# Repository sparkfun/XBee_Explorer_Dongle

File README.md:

SparkFun XBee Explorer Dongle
========================================

[*SparkFun XBee Explorer Dongle (WRL-11697)*](https://www.sparkfun.com/products/11697)

With the XBee Explorer Dongle you can plug the unit directly into your USB port 
and have it act as a gateway between your computer and the XBee. It has the FT231X USB-to-serial converter IC on board. 

Repository Contents
-------------------
* **/Hardware** - All Eagle design files (.brd, .sch, .STL)
* **/Production** - Test bed files and production panel files

Documentation
--------------
* **[Hookup Guide](https://learn.sparkfun.com/tutorials/exploring-xbees-and-xctu)** - Basic hookup guide for the XBee Explorer.
* **[SparkFun Fritzing repo](https://github.com/sparkfun/Fritzing_Parts)** - Fritzing diagrams for SparkFun products.
* **[SparkFun 3D Model repo](https://github.com/sparkfun/3D_Models)** - 3D models of SparkFun products. 

Product Versions
----------------
* [WRL-11697](https://www.sparkfun.com/products/11697)- XBee Dongle with the FT232 USB to serial converter, v23. Current.
* [WRL-09819](https://www.sparkfun.com/products/retired/9819)- XBee Dongle with the FT232 USB to serial converter, v12. Retired.

Version History
---------------
* [V_2.3](https://github.com/sparkfun/XBee_Explorer_Dongle/tree/V_2.3) - GitHub files, version 2.3. Current
* [V_2.2](https://github.com/sparkfun/XBee_Explorer_Dongle/tree/V_2.2) - GitHub files, version 2.2
* [V_1.2](https://github.com/sparkfun/XBee_Explorer_Dongle/tree/V_1.2) -GitHub files, version 1.2. 

License Information
-------------------

This product is _**open source**_! 

Please review the LICENSE.md file for license information. 

If you have any questions or concerns on licensing, please contact techsupport@sparkfun.com.

Distributed as-is; no warranty is given.

- Your friends at SparkFun.

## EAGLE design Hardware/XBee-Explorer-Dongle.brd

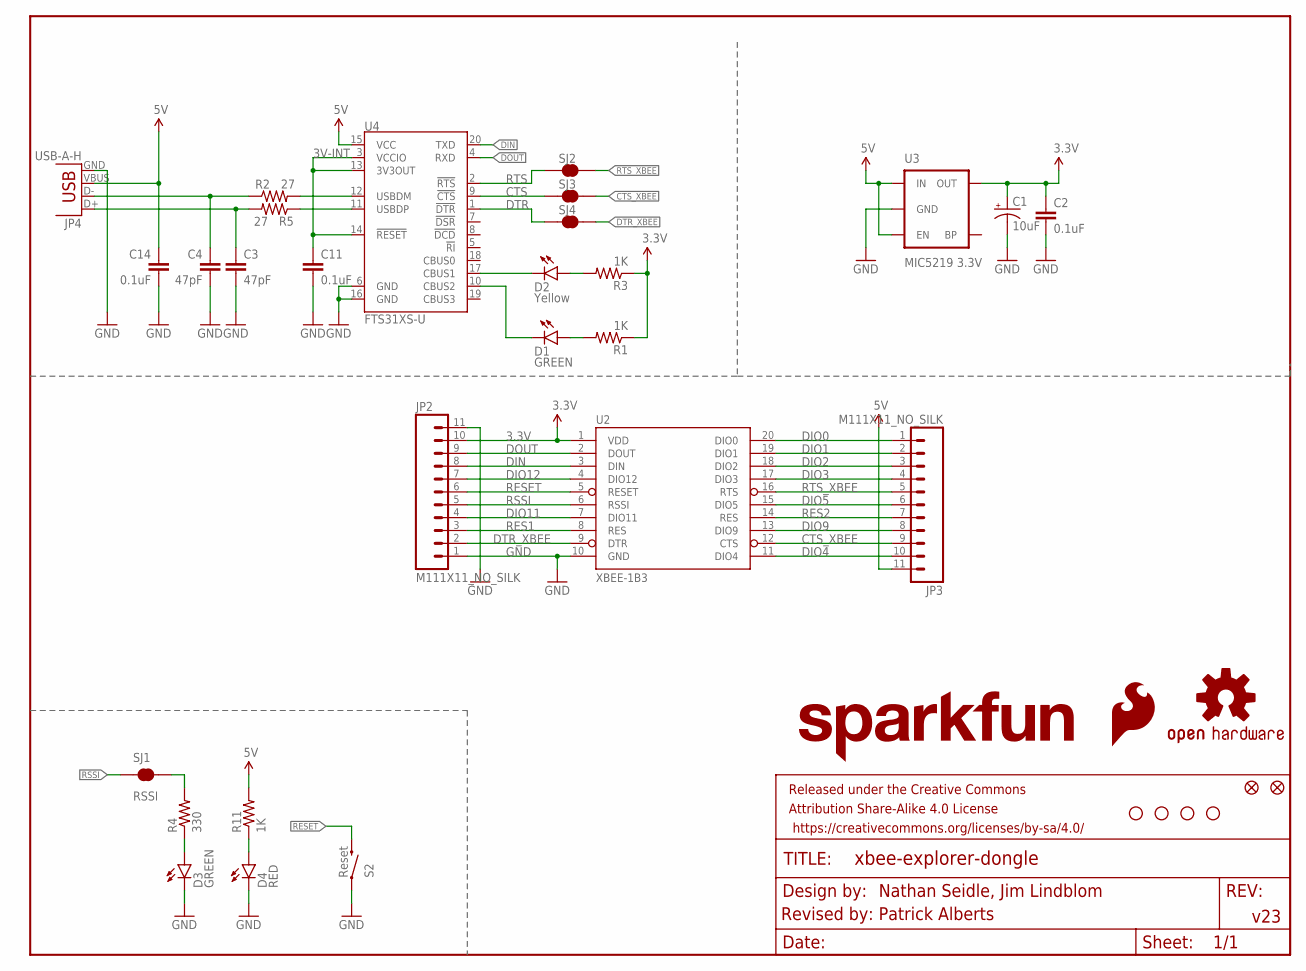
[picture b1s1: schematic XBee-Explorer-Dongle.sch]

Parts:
C1: 10uF; EIA3216
C2, C11, C14: 0.1uF; 0603-CAP
C3, C4: 47pF; 0603-CAP
D1, D3: GREEN; LED-0603
D2: Yellow; LED-0603
D4: RED; LED-0603
FID1, FID2: FIDUCIAL1X2; FIDUCIAL-1X2
FRAME1: FRAME-LETTER; CREATIVE_COMMONS
JP2, JP3: M111X11_NO_SILK; 1X11_NO_SILK
JP4: USB-A-H
LOGO1: SFE_LOGO_FLAME.1_INCH; SFE_LOGO_FLAME_.1
LOGO2: SFE_LOGO_NAME.2_INCH; SFE_LOGO_NAME_.2
R1, R3, R11: 1K; 0603-RES
R2, R5: 27; 0603-RES
R4: 330; 0603-RES
S2: Reset; TACTILE_SWITCH_SMD
SJ1, SJ2, SJ3, SJ4: RSSI; SJ_2S-TRACE
U2: XBEE-1B3; XBEE-SMD
U3: MIC5219 3.3V; SOT23-5
U4: FTS31XS-U; SSOP20_L
U$5, U$9, U$10, U$11: STAND-OFF
U$7: OSHW-LOGOS; OSHW-LOGO-S

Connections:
3.3V: C1.A (+), C2.1, JP2.10, R1.1, R3.1, U2.1 (VDD), U3.5 (OUT)
3V-INT: C11.1, U4.3 (VCCIO), U4.13 (3V3OUT), U4.14 (!RESET)
5V: C14.1, JP3.11, JP4.VBUS, R11.2, U3.1 (IN), U3.3 (EN), U4.15 (VCC)
CTS: SJ3.1, U4.9 (!CTS)
CTS_XBEE: JP3.9, SJ3.2, U2.12 (CTS)
DIN: JP2.8, U2.3 (DIN), U4.20 (TXD)
DIO0: JP3.1, U2.20 (DIO0)
DIO1: JP3.2, U2.19 (DIO1)
DIO2: JP3.3, U2.18 (DIO2)
DIO3: JP3.4, U2.17 (DIO3)
DIO4: JP3.10, U2.11 (DIO4)
DIO5: JP3.6, U2.15 (DIO5)
DIO9: JP3.8, U2.13 (DIO9)
DIO11: JP2.4, U2.7 (DIO11)
DIO12: JP2.7, U2.4 (DIO12)
DOUT: JP2.9, U2.2 (DOUT), U4.4 (RXD)
DTR: SJ4.1, U4.1 (!DTR)
DTR_XBEE: JP2.2, SJ4.2, U2.9 (DTR)
GND: C1.C (-), C2.2, C3.2, C4.2, C11.2, C14.2, D3.C, D4.C, JP2.1, JP2.11, JP4.GND, S2.1, U2.10 (GND), U3.2 (GND), U4.6 (GND), U4.16 (GND)
unnamed: D1.A, R1.2
unnamed: D3.A, R4.1
unnamed: C4.1, JP4.D-, R2.1
unnamed: D2.A, R3.2
unnamed: R2.2, U4.12 (USBDM)
unnamed: C3.1, JP4.D+, R5.2
unnamed: R5.1, U4.11 (USBDP)
unnamed: R4.2, SJ1.2
unnamed: D4.A, R11.1
RES1: JP2.3, U2.8 (RES)
RES2: JP3.7, U2.14 (RES)
RESET: JP2.6, S2.3 (2), U2.5 (RESET)
RSSI: JP2.5, SJ1.1, U2.6 (RSSI)
RTS: SJ2.1, U4.2 (!RTS)
RTS_XBEE: JP3.5, SJ2.2, U2.16 (RTS)
RXLED: D2.C, U4.17 (CBUS1)
TXLED: D1.C, U4.10 (CBUS2)

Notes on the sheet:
Nathan Seidle, Jim Lindblom
v23
Revised by: Patrick Alberts

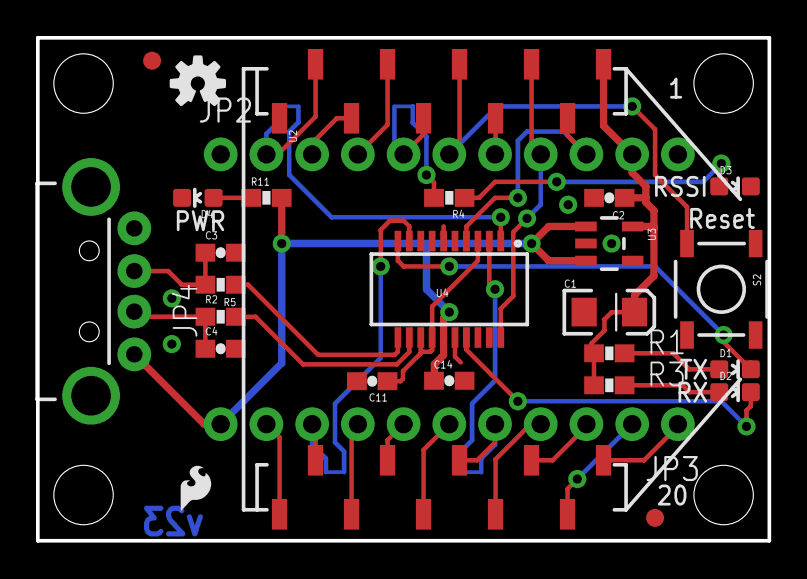
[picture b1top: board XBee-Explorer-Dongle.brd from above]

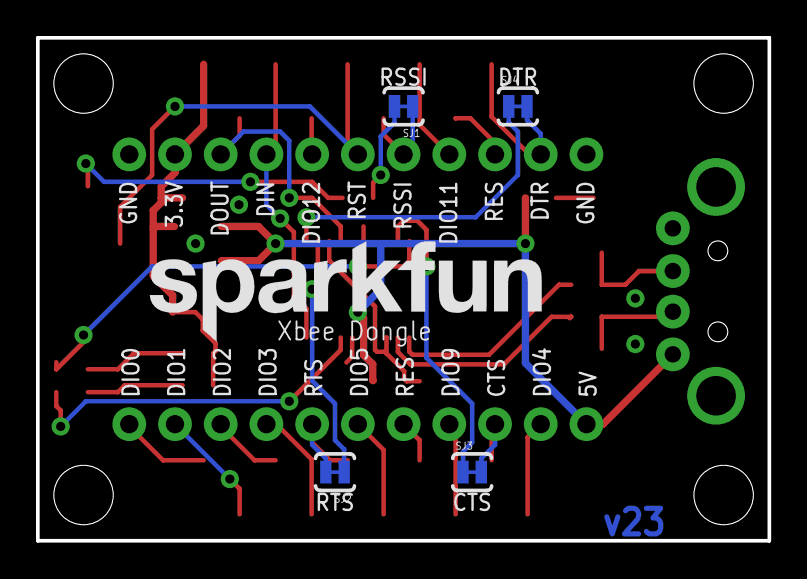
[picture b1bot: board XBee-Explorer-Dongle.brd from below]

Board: 2 copper layers, 40.6 x 27.9 mm, 37 parts (5 on the bottom side), 36 nets.

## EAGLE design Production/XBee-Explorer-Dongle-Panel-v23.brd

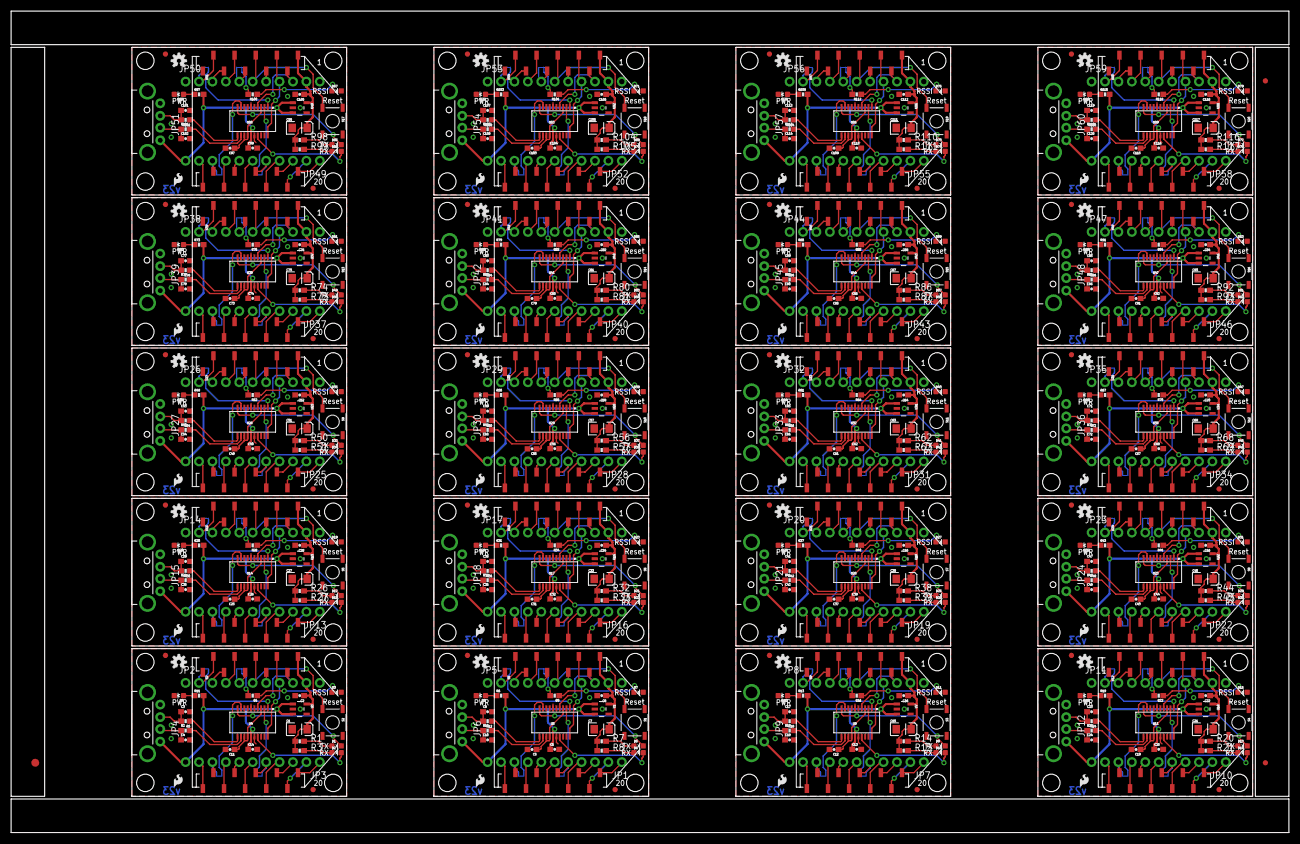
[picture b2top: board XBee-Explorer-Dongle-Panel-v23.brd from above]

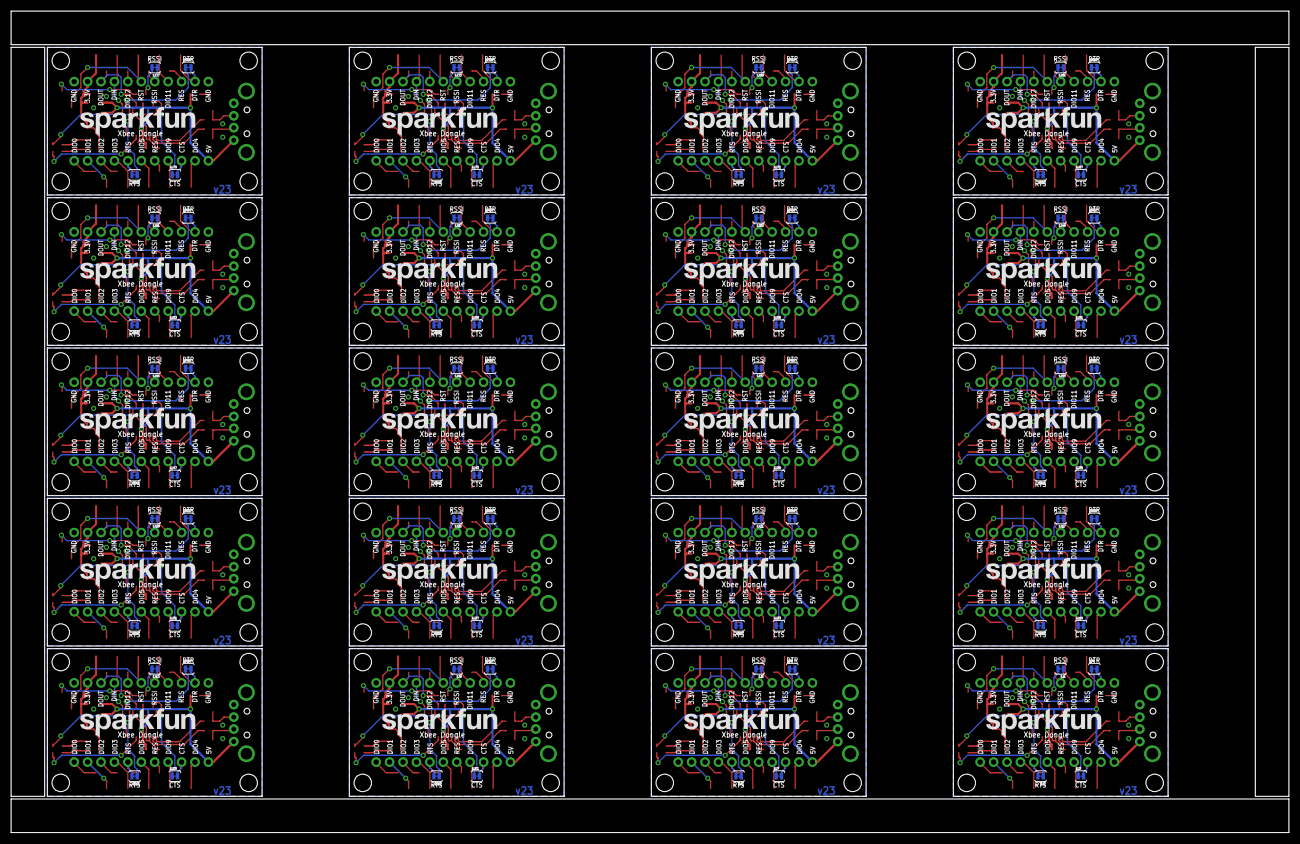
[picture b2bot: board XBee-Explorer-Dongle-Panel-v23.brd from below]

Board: 2 copper layers, 241.8 x 155.4 mm, 723 parts (100 on the bottom side), 720 nets.

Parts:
C1, C7, C15, C21, C27, C33, C39, C45, C51, C57, C63, C69, C75, C81, C87, C93, C99, C105, C111, C117: 10uF; EIA3216
C2, C5, C6, C8, C11, C12, C13, C14, C16, C19, C20, C22, C25, C26, C28, C31, C32, C34, C37, C38, C40, C43, C44, C46, C49, C50, C52, C55, C56, C58, C61, C62, C64, C67, C68, C70, C73, C74, C76, C79, C80, C82, C85, C86, C88, C91, C92, C94, C97, C98, C100, C103, C104, C106, C109, C110, C112, C115, C116, C118: 0.1uF; 0603-CAP
C3, C4, C9, C10, C17, C18, C23, C24, C29, C30, C35, C36, C41, C42, C47, C48, C53, C54, C59, C60, C65, C66, C71, C72, C77, C78, C83, C84, C89, C90, C95, C96, C101, C102, C107, C108, C113, C114, C119, C120: 47pF; 0603-CAP
D1, D3, D5, D7, D9, D11, D13, D15, D17, D19, D21, D23, D25, D27, D29, D31, D33, D35, D37, D39, D41, D43, D45, D47, D49, D51, D53, D55, D57, D59, D61, D63, D65, D67, D69, D71, D73, D75, D77, D79: GREEN; LED-0603
D2, D6, D10, D14, D18, D22, D26, D30, D34, D38, D42, D46, D50, D54, D58, D62, D66, D70, D74, D78: Yellow; LED-0603
D4, D8, D12, D16, D20, D24, D28, D32, D36, D40, D44, D48, D52, D56, D60, D64, D68, D72, D76, D80: RED; LED-0603
E$1: FIDUCIAL-1.5X3
E$5, E$6: FIDUCIAL-1X2
FID1, FID2, FID3, FID4, FID5, FID6, FID7, FID8, FID9, FID10, FID11, FID12, FID13, FID14, FID15, FID16, FID17, FID18, FID19, FID20, FID21, FID22, FID23, FID24, FID25, FID26, FID27, FID28, FID29, FID30, FID31, FID32, FID33, FID34, FID35, FID36, FID37, FID38, FID39, FID40: FIDUCIAL1X2; FIDUCIAL-1X2
JP1, JP2, JP3, JP5, JP7, JP8, JP10, JP11, JP13, JP14, JP16, JP17, JP19, JP20, JP22, JP23, JP25, JP26, JP28, JP29, JP31, JP32, JP34, JP35, JP37, JP38, JP40, JP41, JP43, JP44, JP46, JP47, JP49, JP50, JP52, JP53, JP55, JP56, JP58, JP59: M111X11_NO_SILK; 1X11_NO_SILK
JP4, JP6, JP9, JP12, JP15, JP18, JP21, JP24, JP27, JP30, JP33, JP36, JP39, JP42, JP45, JP48, JP51, JP54, JP57, JP60: USB-A-H
LOGO1, LOGO3, LOGO5, LOGO7, LOGO9, LOGO11, LOGO13, LOGO15, LOGO17, LOGO19, LOGO21, LOGO23, LOGO25, LOGO27, LOGO29, LOGO31, LOGO33, LOGO35, LOGO37, LOGO39: SFE_LOGO_FLAME.1_INCH; SFE_LOGO_FLAME_.1
LOGO2, LOGO4, LOGO6, LOGO8, LOGO10, LOGO12, LOGO14, LOGO16, LOGO18, LOGO20, LOGO22, LOGO24, LOGO26, LOGO28, LOGO30, LOGO32, LOGO34, LOGO36, LOGO38, LOGO40: SFE_LOGO_NAME.2_INCH; SFE_LOGO_NAME_.2
R1, R3, R6, R7, R8, R11, R13, R14, R15, R19, R20, R21, R25, R26, R27, R31, R32, R33, R37, R38, R39, R43, R44, R45, R49, R50, R51, R55, R56, R57, R61, R62, R63, R67, R68, R69, R73, R74, R75, R79, R80, R81, R85, R86, R87, R91, R92, R93, R97, R98, R99, R103, R104, R105, R109, R110, R111, R115, R116, R117: 1K; 0603-RES
R2, R5, R10, R12, R17, R18, R23, R24, R29, R30, R35, R36, R41, R42, R47, R48, R53, R54, R59, R60, R65, R66, R71, R72, R77, R78, R83, R84, R89, R90, R95, R96, R101, R102, R107, R108, R113, R114, R119, R120: 27; 0603-RES
R4, R9, R16, R22, R28, R34, R40, R46, R52, R58, R64, R70, R76, R82, R88, R94, R100, R106, R112, R118: 330; 0603-RES
S1, S2, S3, S4, S5, S6, S7, S8, S9, S10, S11, S12, S13, S14, S15, S16, S17, S18, S19, S20: Reset; TACTILE_SWITCH_SMD
SJ1, SJ2, SJ3, SJ4, SJ5, SJ6, SJ7, SJ8, SJ9, SJ10, SJ11, SJ12, SJ13, SJ14, SJ15, SJ16, SJ17, SJ18, SJ19, SJ20, SJ21, SJ22, SJ23, SJ24, SJ25, SJ26, SJ27, SJ28, SJ29, SJ30, SJ31, SJ32, SJ33, SJ34, SJ35, SJ36, SJ37, SJ38, SJ39, SJ40, SJ41, SJ42, SJ43, SJ44, SJ45, SJ46, SJ47, SJ48, SJ49, SJ50, SJ51, SJ52, SJ53, SJ54, SJ55, SJ56, SJ57, SJ58, SJ59, SJ60, SJ61, SJ62, SJ63, SJ64, SJ65, SJ66, SJ67, SJ68, SJ69, SJ70, SJ71, SJ72, SJ73, SJ74, SJ75, SJ76, SJ77, SJ78, SJ79, SJ80: RSSI; SJ_2S-TRACE
U1, U3, U7, U10, U13, U16, U19, U22, U25, U28, U31, U34, U37, U40, U43, U46, U49, U52, U55, U58: MIC5219 3.3V; SOT23-5
U2, U6, U9, U12, U15, U18, U21, U24, U27, U30, U33, U36, U39, U42, U45, U48, U51, U54, U57, U60: XBEE-1B3; XBEE-SMD
U4, U5, U8, U11, U14, U17, U20, U23, U26, U29, U32, U35, U38, U41, U44, U47, U50, U53, U56, U59: FTS31XS-U; SSOP20_L
U$1, U$2, U$3, U$4, U$5, U$8, U$9, U$10, U$11, U$12, U$13, U$14, U$16, U$17, U$18, U$19, U$21, U$22, U$23, U$24, U$26, U$27, U$28, U$29, U$31, U$32, U$33, U$34, U$36, U$37, U$38, U$39, U$41, U$42, U$43, U$44, U$46, U$47, U$48, U$49, U$51, U$52, U$53, U$54, U$56, U$57, U$58, U$59, U$61, U$62, U$63, U$64, U$66, U$67, U$68, U$69, U$71, U$72, U$73, U$74, U$76, U$77, U$78, U$79, U$81, U$82, U$83, U$84, U$86, U$87, U$88, U$89, U$91, U$92, U$93, U$94, U$96, U$97, U$98, U$99: STAND-OFF
U$6, U$7, U$15, U$20, U$25, U$30, U$35, U$40, U$45, U$50, U$55, U$60, U$65, U$70, U$75, U$80, U$85, U$90, U$95, U$100: OSHW-LOGOS; OSHW-LOGO-S

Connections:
3.3V: C1.A, C2.1, JP2.10, R1.1, R3.1, U2.1, U3.5
3.3V1: C7.A, C8.1, JP5.10, R7.1, R8.1, U1.5, U6.1
3.3V2: C15.A, C16.1, JP8.10, R14.1, R15.1, U7.5, U9.1
3.3V3: C21.A, C22.1, JP11.10, R20.1, R21.1, U10.5, U12.1
3.3V4: C27.A, C28.1, JP14.10, R26.1, R27.1, U13.5, U15.1
3.3V5: C33.A, C34.1, JP17.10, R32.1, R33.1, U16.5, U18.1
3.3V6: C39.A, C40.1, JP20.10, R38.1, R39.1, U19.5, U21.1
3.3V7: C45.A, C46.1, JP23.10, R44.1, R45.1, U22.5, U24.1
3.3V8: C51.A, C52.1, JP26.10, R50.1, R51.1, U25.5, U27.1
3.3V9: C57.A, C58.1, JP29.10, R56.1, R57.1, U28.5, U30.1
3.3V10: C63.A, C64.1, JP32.10, R62.1, R63.1, U31.5, U33.1
3.3V11: C69.A, C70.1, JP35.10, R68.1, R69.1, U34.5, U36.1
3.3V12: C75.A, C76.1, JP38.10, R74.1, R75.1, U37.5, U39.1
3.3V13: C81.A, C82.1, JP41.10, R80.1, R81.1, U40.5, U42.1
3.3V14: C87.A, C88.1, JP44.10, R86.1, R87.1, U43.5, U45.1
3.3V15: C93.A, C94.1, JP47.10, R92.1, R93.1, U46.5, U48.1
3.3V16: C99.A, C100.1, JP50.10, R98.1, R99.1, U49.5, U51.1
3.3V17: C105.A, C106.1, JP53.10, R104.1, R105.1, U52.5, U54.1
3.3V18: C111.A, C112.1, JP56.10, R110.1, R111.1, U55.5, U57.1
3.3V19: C117.A, C118.1, JP59.10, R116.1, R117.1, U58.5, U60.1
3V-INT: C11.1, U4.3, U4.13, U4.14
3V-INT1: C5.1, U5.3, U5.13, U5.14
3V-INT2: C12.1, U8.3, U8.13, U8.14
3V-INT3: C19.1, U11.3, U11.13, U11.14
3V-INT4: C25.1, U14.3, U14.13, U14.14
3V-INT5: C31.1, U17.3, U17.13, U17.14
3V-INT6: C37.1, U20.3, U20.13, U20.14
3V-INT7: C43.1, U23.3, U23.13, U23.14
3V-INT8: C49.1, U26.3, U26.13, U26.14
3V-INT9: C55.1, U29.3, U29.13, U29.14
3V-INT10: C61.1, U32.3, U32.13, U32.14
3V-INT11: C67.1, U35.3, U35.13, U35.14
3V-INT12: C73.1, U38.3, U38.13, U38.14
3V-INT13: C79.1, U41.3, U41.13, U41.14
3V-INT14: C85.1, U44.3, U44.13, U44.14
3V-INT15: C91.1, U47.3, U47.13, U47.14
3V-INT16: C97.1, U50.3, U50.13, U50.14
3V-INT17: C103.1, U53.3, U53.13, U53.14
3V-INT18: C109.1, U56.3, U56.13, U56.14
3V-INT19: C115.1, U59.3, U59.13, U59.14
5V: C14.1, JP3.11, JP4.VBUS, R11.2, U3.1, U3.3, U4.15
5V1: C6.1, JP1.11, JP6.VBUS, R6.2, U1.1, U1.3, U5.15
5V2: C13.1, JP7.11, JP9.VBUS, R13.2, U7.1, U7.3, U8.15
5V3: C20.1, JP10.11, JP12.VBUS, R19.2, U10.1, U10.3, U11.15
5V4: C26.1, JP13.11, JP15.VBUS, R25.2, U13.1, U13.3, U14.15
5V5: C32.1, JP16.11, JP18.VBUS, R31.2, U16.1, U16.3, U17.15
5V6: C38.1, JP19.11, JP21.VBUS, R37.2, U19.1, U19.3, U20.15
5V7: C44.1, JP22.11, JP24.VBUS, R43.2, U22.1, U22.3, U23.15
5V8: C50.1, JP25.11, JP27.VBUS, R49.2, U25.1, U25.3, U26.15
5V9: C56.1, JP28.11, JP30.VBUS, R55.2, U28.1, U28.3, U29.15
5V10: C62.1, JP31.11, JP33.VBUS, R61.2, U31.1, U31.3, U32.15
5V11: C68.1, JP34.11, JP36.VBUS, R67.2, U34.1, U34.3, U35.15
5V12: C74.1, JP37.11, JP39.VBUS, R73.2, U37.1, U37.3, U38.15
5V13: C80.1, JP40.11, JP42.VBUS, R79.2, U40.1, U40.3, U41.15
5V14: C86.1, JP43.11, JP45.VBUS, R85.2, U43.1, U43.3, U44.15
5V15: C92.1, JP46.11, JP48.VBUS, R91.2, U46.1, U46.3, U47.15
5V16: C98.1, JP49.11, JP51.VBUS, R97.2, U49.1, U49.3, U50.15
5V17: C104.1, JP52.11, JP54.VBUS, R103.2, U52.1, U52.3, U53.15
5V18: C110.1, JP55.11, JP57.VBUS, R109.2, U55.1, U55.3, U56.15
5V19: C116.1, JP58.11, JP60.VBUS, R115.2, U58.1, U58.3, U59.15
CTS: SJ3.1, U4.9
CTS1: SJ7.1, U5.9
CTS2: SJ11.1, U8.9
CTS3: SJ15.1, U11.9
CTS4: SJ19.1, U14.9
CTS5: SJ23.1, U17.9
CTS6: SJ27.1, U20.9
CTS7: SJ31.1, U23.9
CTS8: SJ35.1, U26.9
CTS9: SJ39.1, U29.9
CTS10: SJ43.1, U32.9
CTS11: SJ47.1, U35.9
CTS12: SJ51.1, U38.9
CTS13: SJ55.1, U41.9
CTS14: SJ59.1, U44.9
CTS15: SJ63.1, U47.9
CTS16: SJ67.1, U50.9
CTS17: SJ71.1, U53.9
CTS18: SJ75.1, U56.9
CTS19: SJ79.1, U59.9
CTS_XBEE: JP3.9, SJ3.2, U2.12
CTS_XBEE1: JP1.9, SJ7.2, U6.12
CTS_XBEE2: JP7.9, SJ11.2, U9.12
CTS_XBEE3: JP10.9, SJ15.2, U12.12
CTS_XBEE4: JP13.9, SJ19.2, U15.12
CTS_XBEE5: JP16.9, SJ23.2, U18.12
CTS_XBEE6: JP19.9, SJ27.2, U21.12
CTS_XBEE7: JP22.9, SJ31.2, U24.12
CTS_XBEE8: JP25.9, SJ35.2, U27.12
CTS_XBEE9: JP28.9, SJ39.2, U30.12
CTS_XBEE10: JP31.9, SJ43.2, U33.12
CTS_XBEE11: JP34.9, SJ47.2, U36.12
CTS_XBEE12: JP37.9, SJ51.2, U39.12
CTS_XBEE13: JP40.9, SJ55.2, U42.12
CTS_XBEE14: JP43.9, SJ59.2, U45.12
CTS_XBEE15: JP46.9, SJ63.2, U48.12
CTS_XBEE16: JP49.9, SJ67.2, U51.12
CTS_XBEE17: JP52.9, SJ71.2, U54.12
CTS_XBEE18: JP55.9, SJ75.2, U57.12
CTS_XBEE19: JP58.9, SJ79.2, U60.12
DIN: JP2.8, U2.3, U4.20
DIN1: JP5.8, U5.20, U6.3
DIN2: JP8.8, U8.20, U9.3
DIN3: JP11.8, U11.20, U12.3
DIN4: JP14.8, U14.20, U15.3
DIN5: JP17.8, U17.20, U18.3
DIN6: JP20.8, U20.20, U21.3
DIN7: JP23.8, U23.20, U24.3
DIN8: JP26.8, U26.20, U27.3
DIN9: JP29.8, U29.20, U30.3
DIN10: JP32.8, U32.20, U33.3
DIN11: JP35.8, U35.20, U36.3
DIN12: JP38.8, U38.20, U39.3
DIN13: JP41.8, U41.20, U42.3
DIN14: JP44.8, U44.20, U45.3
DIN15: JP47.8, U47.20, U48.3
DIN16: JP50.8, U50.20, U51.3
DIN17: JP53.8, U53.20, U54.3
DIN18: JP56.8, U56.20, U57.3
DIN19: JP59.8, U59.20, U60.3
DIO0: JP3.1, U2.20
DIO1: JP3.2, U2.19
DIO2: JP3.3, U2.18
DIO3: JP3.4, U2.17
DIO4: JP3.10, U2.11
DIO5: JP3.6, U2.15
DIO6: JP1.10, U6.11
DIO7: JP1.8, U6.13
DIO8: JP1.6, U6.15
DIO9: JP3.8, U2.13
DIO10: JP1.4, U6.17
DIO11: JP2.4, U2.7
DIO12: JP2.7, U2.4
DIO13: JP1.3, U6.18
DIO14: JP1.2, U6.19
DIO15: JP1.1, U6.20
DIO16: JP5.4, U6.7
DIO17: JP5.7, U6.4
DIO18: JP7.10, U9.11
DIO19: JP7.8, U9.13
DIO20: JP7.6, U9.15
DIO21: JP7.4, U9.17
DIO22: JP7.3, U9.18
DIO23: JP7.2, U9.19
DIO24: JP7.1, U9.20
DIO25: JP8.4, U9.7
DIO26: JP8.7, U9.4
DIO27: JP10.10, U12.11
DIO28: JP10.8, U12.13
DIO29: JP10.6, U12.15
DIO30: JP10.4, U12.17
DIO31: JP10.3, U12.18
DIO32: JP10.2, U12.19
DIO33: JP10.1, U12.20
DIO34: JP11.4, U12.7
DIO35: JP11.7, U12.4
DIO36: JP13.10, U15.11
DIO37: JP13.8, U15.13
DIO38: JP13.6, U15.15
DIO39: JP13.4, U15.17
DIO40: JP13.3, U15.18
DIO41: JP13.2, U15.19
DIO42: JP13.1, U15.20
DIO43: JP14.4, U15.7
DIO44: JP14.7, U15.4
DIO45: JP16.10, U18.11
DIO46: JP16.8, U18.13
DIO47: JP16.6, U18.15
DIO48: JP16.4, U18.17
DIO49: JP16.3, U18.18
DIO50: JP16.2, U18.19
DIO51: JP16.1, U18.20
DIO52: JP17.4, U18.7
DIO53: JP17.7, U18.4
DIO54: JP19.10, U21.11
DIO55: JP19.8, U21.13
DIO56: JP19.6, U21.15
DIO57: JP19.4, U21.17
DIO58: JP19.3, U21.18
DIO59: JP19.2, U21.19
DIO60: JP19.1, U21.20
DIO61: JP20.4, U21.7
DIO62: JP20.7, U21.4
DIO63: JP22.10, U24.11
DIO64: JP22.8, U24.13
DIO65: JP22.6, U24.15
DIO66: JP22.4, U24.17
DIO67: JP22.3, U24.18
DIO68: JP22.2, U24.19
DIO69: JP22.1, U24.20
DIO70: JP23.4, U24.7
DIO71: JP23.7, U24.4
DIO72: JP25.10, U27.11
DIO73: JP25.8, U27.13
DIO74: JP25.6, U27.15
DIO75: JP25.4, U27.17
DIO76: JP25.3, U27.18
DIO77: JP25.2, U27.19
DIO78: JP25.1, U27.20
DIO79: JP26.4, U27.7
DIO80: JP26.7, U27.4
DIO81: JP28.10, U30.11
DIO82: JP28.8, U30.13
DIO83: JP28.6, U30.15
DIO84: JP28.4, U30.17
DIO85: JP28.3, U30.18
DIO86: JP28.2, U30.19
DIO87: JP28.1, U30.20
DIO88: JP29.4, U30.7
DIO89: JP29.7, U30.4
DIO90: JP31.10, U33.11
DIO91: JP31.8, U33.13
DIO92: JP31.6, U33.15
DIO93: JP31.4, U33.17
DIO94: JP31.3, U33.18
DIO95: JP31.2, U33.19
DIO96: JP31.1, U33.20
DIO97: JP32.4, U33.7
DIO98: JP32.7, U33.4
DIO99: JP34.10, U36.11
DIO100: JP34.8, U36.13
DIO101: JP34.6, U36.15
DIO102: JP34.4, U36.17
DIO103: JP34.3, U36.18
DIO104: JP34.2, U36.19
DIO105: JP34.1, U36.20
DIO106: JP35.4, U36.7
DIO107: JP35.7, U36.4
DIO108: JP37.10, U39.11
DIO109: JP37.8, U39.13
DIO110: JP37.6, U39.15
DIO111: JP37.4, U39.17
DIO112: JP37.3, U39.18
DIO113: JP37.2, U39.19
DIO114: JP37.1, U39.20
DIO115: JP38.4, U39.7
DIO116: JP38.7, U39.4
DIO117: JP40.10, U42.11
DIO118: JP40.8, U42.13
DIO119: JP40.6, U42.15
DIO120: JP40.4, U42.17
DIO121: JP40.3, U42.18
DIO122: JP40.2, U42.19
DIO123: JP40.1, U42.20
DIO124: JP41.4, U42.7
DIO125: JP41.7, U42.4
DIO126: JP43.10, U45.11
DIO127: JP43.8, U45.13
DIO128: JP43.6, U45.15
DIO129: JP43.4, U45.17
DIO130: JP43.3, U45.18
DIO131: JP43.2, U45.19
DIO132: JP43.1, U45.20
DIO133: JP44.4, U45.7
DIO134: JP44.7, U45.4
DIO135: JP46.10, U48.11
DIO136: JP46.8, U48.13
DIO137: JP46.6, U48.15
DIO138: JP46.4, U48.17
DIO139: JP46.3, U48.18
DIO140: JP46.2, U48.19
DIO141: JP46.1, U48.20
DIO142: JP47.4, U48.7
DIO143: JP47.7, U48.4
DIO144: JP49.10, U51.11
DIO145: JP49.8, U51.13
DIO146: JP49.6, U51.15
DIO147: JP49.4, U51.17
DIO148: JP49.3, U51.18
DIO149: JP49.2, U51.19
DIO150: JP49.1, U51.20
DIO151: JP50.4, U51.7
DIO152: JP50.7, U51.4
DIO153: JP52.10, U54.11
DIO154: JP52.8, U54.13
DIO155: JP52.6, U54.15
DIO156: JP52.4, U54.17
DIO157: JP52.3, U54.18
DIO158: JP52.2, U54.19
DIO159: JP52.1, U54.20
DIO160: JP53.4, U54.7
DIO161: JP53.7, U54.4
DIO162: JP55.10, U57.11
DIO163: JP55.8, U57.13
DIO164: JP55.6, U57.15
DIO165: JP55.4, U57.17
DIO166: JP55.3, U57.18
DIO167: JP55.2, U57.19
DIO168: JP55.1, U57.20
DIO169: JP56.4, U57.7
DIO170: JP56.7, U57.4
DIO171: JP58.10, U60.11
DIO172: JP58.8, U60.13
DIO173: JP58.6, U60.15
DIO174: JP58.4, U60.17
DIO175: JP58.3, U60.18
DIO176: JP58.2, U60.19
DIO177: JP58.1, U60.20
DIO178: JP59.4, U60.7
DIO179: JP59.7, U60.4
DOUT: JP2.9, U2.2, U4.4
DOUT1: JP5.9, U5.4, U6.2
DOUT2: JP8.9, U8.4, U9.2
DOUT3: JP11.9, U11.4, U12.2
DOUT4: JP14.9, U14.4, U15.2
DOUT5: JP17.9, U17.4, U18.2
DOUT6: JP20.9, U20.4, U21.2
DOUT7: JP23.9, U23.4, U24.2
DOUT8: JP26.9, U26.4, U27.2
DOUT9: JP29.9, U29.4, U30.2
DOUT10: JP32.9, U32.4, U33.2
DOUT11: JP35.9, U35.4, U36.2
DOUT12: JP38.9, U38.4, U39.2
DOUT13: JP41.9, U41.4, U42.2
DOUT14: JP44.9, U44.4, U45.2
DOUT15: JP47.9, U47.4, U48.2
DOUT16: JP50.9, U50.4, U51.2
DOUT17: JP53.9, U53.4, U54.2
DOUT18: JP56.9, U56.4, U57.2
DOUT19: JP59.9, U59.4, U60.2
DTR: SJ4.1, U4.1
DTR1: SJ8.1, U5.1
DTR2: SJ12.1, U8.1
DTR3: SJ16.1, U11.1
DTR4: SJ20.1, U14.1
DTR5: SJ24.1, U17.1
DTR6: SJ28.1, U20.1
DTR7: SJ32.1, U23.1
DTR8: SJ36.1, U26.1
DTR9: SJ40.1, U29.1
DTR10: SJ44.1, U32.1
DTR11: SJ48.1, U35.1
DTR12: SJ52.1, U38.1
DTR13: SJ56.1, U41.1
DTR14: SJ60.1, U44.1
DTR15: SJ64.1, U47.1
DTR16: SJ68.1, U50.1
DTR17: SJ72.1, U53.1
DTR18: SJ76.1, U56.1
DTR19: SJ80.1, U59.1
DTR_XBEE: JP2.2, SJ4.2, U2.9
DTR_XBEE1: JP5.2, SJ8.2, U6.9
DTR_XBEE2: JP8.2, SJ12.2, U9.9
DTR_XBEE3: JP11.2, SJ16.2, U12.9
DTR_XBEE4: JP14.2, SJ20.2, U15.9
DTR_XBEE5: JP17.2, SJ24.2, U18.9
DTR_XBEE6: JP20.2, SJ28.2, U21.9
DTR_XBEE7: JP23.2, SJ32.2, U24.9
DTR_XBEE8: JP26.2, SJ36.2, U27.9
DTR_XBEE9: JP29.2, SJ40.2, U30.9
DTR_XBEE10: JP32.2, SJ44.2, U33.9
DTR_XBEE11: JP35.2, SJ48.2, U36.9
DTR_XBEE12: JP38.2, SJ52.2, U39.9
DTR_XBEE13: JP41.2, SJ56.2, U42.9
DTR_XBEE14: JP44.2, SJ60.2, U45.9
DTR_XBEE15: JP47.2, SJ64.2, U48.9
DTR_XBEE16: JP50.2, SJ68.2, U51.9
DTR_XBEE17: JP53.2, SJ72.2, U54.9
DTR_XBEE18: JP56.2, SJ76.2, U57.9
DTR_XBEE19: JP59.2, SJ80.2, U60.9
GND: C1.C, C2.2, C3.2, C4.2, C11.2, C14.2, D3.C, D4.C, JP2.1, JP2.11, JP4.GND, S2.1, U2.10, U3.2, U4.6, U4.16
GND1: C5.2, C6.2, C7.C, C8.2, C9.2, C10.2, D7.C, D8.C, JP5.1, JP5.11, JP6.GND, S1.1, U1.2, U5.6, U5.16, U6.10
GND2: C12.2, C13.2, C15.C, C16.2, C17.2, C18.2, D11.C, D12.C, JP8.1, JP8.11, JP9.GND, S3.1, U7.2, U8.6, U8.16, U9.10
GND3: C19.2, C20.2, C21.C, C22.2, C23.2, C24.2, D15.C, D16.C, JP11.1, JP11.11, JP12.GND, S4.1, U10.2, U11.6, U11.16, U12.10
GND4: C25.2, C26.2, C27.C, C28.2, C29.2, C30.2, D19.C, D20.C, JP14.1, JP14.11, JP15.GND, S5.1, U13.2, U14.6, U14.16, U15.10
GND5: C31.2, C32.2, C33.C, C34.2, C35.2, C36.2, D23.C, D24.C, JP17.1, JP17.11, JP18.GND, S6.1, U16.2, U17.6, U17.16, U18.10
GND6: C37.2, C38.2, C39.C, C40.2, C41.2, C42.2, D27.C, D28.C, JP20.1, JP20.11, JP21.GND, S7.1, U19.2, U20.6, U20.16, U21.10
GND7: C43.2, C44.2, C45.C, C46.2, C47.2, C48.2, D31.C, D32.C, JP23.1, JP23.11, JP24.GND, S8.1, U22.2, U23.6, U23.16, U24.10
GND8: C49.2, C50.2, C51.C, C52.2, C53.2, C54.2, D35.C, D36.C, JP26.1, JP26.11, JP27.GND, S9.1, U25.2, U26.6, U26.16, U27.10
GND9: C55.2, C56.2, C57.C, C58.2, C59.2, C60.2, D39.C, D40.C, JP29.1, JP29.11, JP30.GND, S10.1, U28.2, U29.6, U29.16, U30.10
GND10: C61.2, C62.2, C63.C, C64.2, C65.2, C66.2, D43.C, D44.C, JP32.1, JP32.11, JP33.GND, S11.1, U31.2, U32.6, U32.16, U33.10
GND11: C67.2, C68.2, C69.C, C70.2, C71.2, C72.2, D47.C, D48.C, JP35.1, JP35.11, JP36.GND, S12.1, U34.2, U35.6, U35.16, U36.10
GND12: C73.2, C74.2, C75.C, C76.2, C77.2, C78.2, D51.C, D52.C, JP38.1, JP38.11, JP39.GND, S13.1, U37.2, U38.6, U38.16, U39.10
GND13: C79.2, C80.2, C81.C, C82.2, C83.2, C84.2, D55.C, D56.C, JP41.1, JP41.11, JP42.GND, S14.1, U40.2, U41.6, U41.16, U42.10
GND14: C85.2, C86.2, C87.C, C88.2, C89.2, C90.2, D59.C, D60.C, JP44.1, JP44.11, JP45.GND, S15.1, U43.2, U44.6, U44.16, U45.10
GND15: C91.2, C92.2, C93.C, C94.2, C95.2, C96.2, D63.C, D64.C, JP47.1, JP47.11, JP48.GND, S16.1, U46.2, U47.6, U47.16, U48.10
GND16: C97.2, C98.2, C99.C, C100.2, C101.2, C102.2, D67.C, D68.C, JP50.1, JP50.11, JP51.GND, S17.1, U49.2, U50.6, U50.16, U51.10
GND17: C103.2, C104.2, C105.C, C106.2, C107.2, C108.2, D71.C, D72.C, JP53.1, JP53.11, JP54.GND, S18.1, U52.2, U53.6, U53.16, U54.10
GND18: C109.2, C110.2, C111.C, C112.2, C113.2, C114.2, D75.C, D76.C, JP56.1, JP56.11, JP57.GND, S19.1, U55.2, U56.6, U56.16, U57.10
GND19: C115.2, C116.2, C117.C, C118.2, C119.2, C120.2, D79.C, D80.C, JP59.1, JP59.11, JP60.GND, S20.1, U58.2, U59.6, U59.16, U60.10
unnamed: D1.A, R1.2
unnamed: D3.A, R4.1
unnamed: C4.1, JP4.D-, R2.1
unnamed: D2.A, R3.2
unnamed: R2.2, U4.12
unnamed: C3.1, JP4.D+, R5.2
unnamed: R5.1, U4.11
unnamed: R4.2, SJ1.2
unnamed: D8.A, R6.1
unnamed: D5.A, R7.2
unnamed: D6.A, R8.2
unnamed: D7.A, R9.1
unnamed: C10.1, JP6.D-, R10.1
unnamed: R10.2, U5.12
unnamed: C9.1, JP6.D+, R12.2
unnamed: R12.1, U5.11
unnamed: R9.2, SJ5.2
unnamed: D12.A, R13.1
unnamed: D9.A, R14.2
unnamed: D10.A, R15.2
unnamed: D11.A, R16.1
unnamed: C18.1, JP9.D-, R17.1
unnamed: R17.2, U8.12
unnamed: C17.1, JP9.D+, R18.2
unnamed: R18.1, U8.11
unnamed: R16.2, SJ9.2
unnamed: D16.A, R19.1
unnamed: D13.A, R20.2
unnamed: D14.A, R21.2
unnamed: D15.A, R22.1
unnamed: C24.1, JP12.D-, R23.1
unnamed: R23.2, U11.12
unnamed: C23.1, JP12.D+, R24.2
unnamed: R24.1, U11.11
unnamed: R22.2, SJ13.2
unnamed: D20.A, R25.1
unnamed: D17.A, R26.2
unnamed: D4.A, R11.1
unnamed: D18.A, R27.2
unnamed: D19.A, R28.1
unnamed: C30.1, JP15.D-, R29.1
unnamed: R29.2, U14.12
unnamed: C29.1, JP15.D+, R30.2
unnamed: R30.1, U14.11
unnamed: R28.2, SJ17.2
unnamed: D24.A, R31.1
unnamed: D21.A, R32.2
unnamed: D22.A, R33.2
unnamed: D23.A, R34.1
unnamed: C36.1, JP18.D-, R35.1
unnamed: R35.2, U17.12
unnamed: C35.1, JP18.D+, R36.2
unnamed: R36.1, U17.11
unnamed: R34.2, SJ21.2
unnamed: D28.A, R37.1
unnamed: D25.A, R38.2
unnamed: D26.A, R39.2
unnamed: D27.A, R40.1
unnamed: C42.1, JP21.D-, R41.1
unnamed: R41.2, U20.12
unnamed: C41.1, JP21.D+, R42.2
unnamed: R42.1, U20.11
unnamed: R40.2, SJ25.2
unnamed: D32.A, R43.1
unnamed: D29.A, R44.2
unnamed: D30.A, R45.2
unnamed: D31.A, R46.1
unnamed: C48.1, JP24.D-, R47.1
unnamed: R47.2, U23.12
unnamed: C47.1, JP24.D+, R48.2
unnamed: R48.1, U23.11
unnamed: R46.2, SJ29.2
unnamed: D36.A, R49.1
unnamed: D33.A, R50.2
unnamed: D34.A, R51.2
unnamed: D35.A, R52.1
unnamed: C54.1, JP27.D-, R53.1
unnamed: R53.2, U26.12
unnamed: C53.1, JP27.D+, R54.2
unnamed: R54.1, U26.11
unnamed: R52.2, SJ33.2
unnamed: D40.A, R55.1
unnamed: D37.A, R56.2
unnamed: D38.A, R57.2
unnamed: D39.A, R58.1
unnamed: C60.1, JP30.D-, R59.1
unnamed: R59.2, U29.12
unnamed: C59.1, JP30.D+, R60.2
unnamed: R60.1, U29.11
unnamed: R58.2, SJ37.2
unnamed: D44.A, R61.1
unnamed: D41.A, R62.2
unnamed: D42.A, R63.2
unnamed: D43.A, R64.1
unnamed: C66.1, JP33.D-, R65.1
unnamed: R65.2, U32.12
unnamed: C65.1, JP33.D+, R66.2
unnamed: R66.1, U32.11
unnamed: R64.2, SJ41.2
unnamed: D48.A, R67.1
unnamed: D45.A, R68.2
unnamed: D46.A, R69.2
unnamed: D47.A, R70.1
unnamed: C72.1, JP36.D-, R71.1
unnamed: R71.2, U35.12
unnamed: C71.1, JP36.D+, R72.2
unnamed: R72.1, U35.11
unnamed: R70.2, SJ45.2
unnamed: D52.A, R73.1
unnamed: D49.A, R74.2
unnamed: D50.A, R75.2
unnamed: D51.A, R76.1
unnamed: C78.1, JP39.D-, R77.1
unnamed: R77.2, U38.12
unnamed: C77.1, JP39.D+, R78.2
unnamed: R78.1, U38.11
unnamed: R76.2, SJ49.2
unnamed: D56.A, R79.1
unnamed: D53.A, R80.2
unnamed: D54.A, R81.2
unnamed: D55.A, R82.1
unnamed: C84.1, JP42.D-, R83.1
unnamed: R83.2, U41.12
unnamed: C83.1, JP42.D+, R84.2
unnamed: R84.1, U41.11
unnamed: R82.2, SJ53.2
unnamed: D60.A, R85.1
unnamed: D57.A, R86.2
unnamed: D58.A, R87.2
unnamed: D59.A, R88.1
unnamed: C90.1, JP45.D-, R89.1
unnamed: R89.2, U44.12
unnamed: C89.1, JP45.D+, R90.2
unnamed: R90.1, U44.11
unnamed: R88.2, SJ57.2
unnamed: D64.A, R91.1
unnamed: D61.A, R92.2
unnamed: D62.A, R93.2
unnamed: D63.A, R94.1
unnamed: C96.1, JP48.D-, R95.1
unnamed: R95.2, U47.12
unnamed: C95.1, JP48.D+, R96.2
unnamed: R96.1, U47.11
unnamed: R94.2, SJ61.2
unnamed: D68.A, R97.1
unnamed: D65.A, R98.2
unnamed: D66.A, R99.2
unnamed: D67.A, R100.1
unnamed: C102.1, JP51.D-, R101.1
unnamed: R101.2, U50.12
unnamed: C101.1, JP51.D+, R102.2
unnamed: R102.1, U50.11
unnamed: R100.2, SJ65.2
unnamed: D72.A, R103.1
unnamed: D69.A, R104.2
unnamed: D70.A, R105.2
unnamed: D71.A, R106.1
unnamed: C108.1, JP54.D-, R107.1
unnamed: R107.2, U53.12
unnamed: C107.1, JP54.D+, R108.2
unnamed: R108.1, U53.11
unnamed: R106.2, SJ69.2
unnamed: D76.A, R109.1
unnamed: D73.A, R110.2
unnamed: D74.A, R111.2
unnamed: D75.A, R112.1
unnamed: C114.1, JP57.D-, R113.1
unnamed: R113.2, U56.12
unnamed: C113.1, JP57.D+, R114.2
unnamed: R114.1, U56.11
unnamed: R112.2, SJ73.2
unnamed: D80.A, R115.1
unnamed: D77.A, R116.2
unnamed: D78.A, R117.2
unnamed: D79.A, R118.1
unnamed: C120.1, JP60.D-, R119.1
unnamed: R119.2, U59.12
unnamed: C119.1, JP60.D+, R120.2
unnamed: R120.1, U59.11
unnamed: R118.2, SJ77.2
RES1: JP2.3, U2.8
RES2: JP3.7, U2.14
RES3: JP5.3, U6.8
RES4: JP1.7, U6.14
RES5: JP8.3, U9.8
RES6: JP7.7, U9.14
RES7: JP11.3, U12.8
RES8: JP10.7, U12.14
RES9: JP14.3, U15.8
RES10: JP13.7, U15.14
RES11: JP17.3, U18.8
RES12: JP16.7, U18.14
RES13: JP20.3, U21.8
RES14: JP19.7, U21.14
RES15: JP23.3, U24.8
RES16: JP22.7, U24.14
RES17: JP26.3, U27.8
RES18: JP25.7, U27.14
RES19: JP29.3, U30.8
RES20: JP28.7, U30.14
RES21: JP32.3, U33.8
RES22: JP31.7, U33.14
RES23: JP35.3, U36.8
RES24: JP34.7, U36.14
RES25: JP38.3, U39.8
RES26: JP37.7, U39.14
RES27: JP41.3, U42.8
RES28: JP40.7, U42.14
RES29: JP44.3, U45.8
RES30: JP43.7, U45.14
RES31: JP47.3, U48.8
RES32: JP46.7, U48.14
RES33: JP50.3, U51.8
RES34: JP49.7, U51.14
RES35: JP53.3, U54.8
RES36: JP52.7, U54.14
RES37: JP56.3, U57.8
RES38: JP55.7, U57.14
RES39: JP59.3, U60.8
RES40: JP58.7, U60.14
RESET: JP2.6, S2.3, U2.5
RESET1: JP5.6, S1.3, U6.5
RESET2: JP8.6, S3.3, U9.5
RESET3: JP11.6, S4.3, U12.5
RESET4: JP14.6, S5.3, U15.5
RESET5: JP17.6, S6.3, U18.5
RESET6: JP20.6, S7.3, U21.5
RESET7: JP23.6, S8.3, U24.5
RESET8: JP26.6, S9.3, U27.5
RESET9: JP29.6, S10.3, U30.5
RESET10: JP32.6, S11.3, U33.5
RESET11: JP35.6, S12.3, U36.5
RESET12: JP38.6, S13.3, U39.5
RESET13: JP41.6, S14.3, U42.5
RESET14: JP44.6, S15.3, U45.5
RESET15: JP47.6, S16.3, U48.5
RESET16: JP50.6, S17.3, U51.5
RESET17: JP53.6, S18.3, U54.5
RESET18: JP56.6, S19.3, U57.5
RESET19: JP59.6, S20.3, U60.5
RSSI: JP2.5, SJ1.1, U2.6
RSSI1: JP5.5, SJ5.1, U6.6
RSSI2: JP8.5, SJ9.1, U9.6
RSSI3: JP11.5, SJ13.1, U12.6
RSSI4: JP14.5, SJ17.1, U15.6
RSSI5: JP17.5, SJ21.1, U18.6
RSSI6: JP20.5, SJ25.1, U21.6
RSSI7: JP23.5, SJ29.1, U24.6
RSSI8: JP26.5, SJ33.1, U27.6
RSSI9: JP29.5, SJ37.1, U30.6
RSSI10: JP32.5, SJ41.1, U33.6
RSSI11: JP35.5, SJ45.1, U36.6
RSSI12: JP38.5, SJ49.1, U39.6
RSSI13: JP41.5, SJ53.1, U42.6
RSSI14: JP44.5, SJ57.1, U45.6
RSSI15: JP47.5, SJ61.1, U48.6
RSSI16: JP50.5, SJ65.1, U51.6
RSSI17: JP53.5, SJ69.1, U54.6
RSSI18: JP56.5, SJ73.1, U57.6
RSSI19: JP59.5, SJ77.1, U60.6
RTS: SJ2.1, U4.2
RTS1: SJ6.1, U5.2
RTS2: SJ10.1, U8.2
RTS3: SJ14.1, U11.2
RTS4: SJ18.1, U14.2
RTS5: SJ22.1, U17.2
RTS6: SJ26.1, U20.2
RTS7: SJ30.1, U23.2
RTS8: SJ34.1, U26.2
RTS9: SJ38.1, U29.2
RTS10: SJ42.1, U32.2
RTS11: SJ46.1, U35.2
RTS12: SJ50.1, U38.2
RTS13: SJ54.1, U41.2
RTS14: SJ58.1, U44.2
RTS15: SJ62.1, U47.2
RTS16: SJ66.1, U50.2
RTS17: SJ70.1, U53.2
RTS18: SJ74.1, U56.2
RTS19: SJ78.1, U59.2
RTS_XBEE: JP3.5, SJ2.2, U2.16
RTS_XBEE1: JP1.5, SJ6.2, U6.16
RTS_XBEE2: JP7.5, SJ10.2, U9.16
RTS_XBEE3: JP10.5, SJ14.2, U12.16
RTS_XBEE4: JP13.5, SJ18.2, U15.16
RTS_XBEE5: JP16.5, SJ22.2, U18.16
RTS_XBEE6: JP19.5, SJ26.2, U21.16
RTS_XBEE7: JP22.5, SJ30.2, U24.16
RTS_XBEE8: JP25.5, SJ34.2, U27.16
RTS_XBEE9: JP28.5, SJ38.2, U30.16
RTS_XBEE10: JP31.5, SJ42.2, U33.16
RTS_XBEE11: JP34.5, SJ46.2, U36.16
RTS_XBEE12: JP37.5, SJ50.2, U39.16
RTS_XBEE13: JP40.5, SJ54.2, U42.16
RTS_XBEE14: JP43.5, SJ58.2, U45.16
RTS_XBEE15: JP46.5, SJ62.2, U48.16
RTS_XBEE16: JP49.5, SJ66.2, U51.16
RTS_XBEE17: JP52.5, SJ70.2, U54.16
RTS_XBEE18: JP55.5, SJ74.2, U57.16
RTS_XBEE19: JP58.5, SJ78.2, U60.16
RXLED: D2.C, U4.17
RXLED1: D6.C, U5.17
RXLED2: D10.C, U8.17
RXLED3: D14.C, U11.17
RXLED4: D18.C, U14.17
RXLED5: D22.C, U17.17
RXLED6: D26.C, U20.17
RXLED7: D30.C, U23.17
RXLED8: D34.C, U26.17
RXLED9: D38.C, U29.17
RXLED10: D42.C, U32.17
RXLED11: D46.C, U35.17
RXLED12: D50.C, U38.17
RXLED13: D54.C, U41.17
RXLED14: D58.C, U44.17
RXLED15: D62.C, U47.17
RXLED16: D66.C, U50.17
RXLED17: D70.C, U53.17
RXLED18: D74.C, U56.17
RXLED19: D78.C, U59.17
TXLED: D1.C, U4.10
TXLED1: D5.C, U5.10
TXLED2: D9.C, U8.10
TXLED3: D13.C, U11.10
TXLED4: D17.C, U14.10
TXLED5: D21.C, U17.10
TXLED6: D25.C, U20.10
TXLED7: D29.C, U23.10
TXLED8: D33.C, U26.10
TXLED9: D37.C, U29.10
TXLED10: D41.C, U32.10
TXLED11: D45.C, U35.10
TXLED12: D49.C, U38.10
TXLED13: D53.C, U41.10
TXLED14: D57.C, U44.10
TXLED15: D61.C, U47.10
TXLED16: D65.C, U50.10
TXLED17: D69.C, U53.10
TXLED18: D73.C, U56.10
TXLED19: D77.C, U59.10

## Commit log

2015-01-21 Deleting USB files
2015-01-21 Adding README with product information
2015-01-21 Fixng README typos
2015-02-11 Upd to usb pth, 0603, sch changes
2015-02-21 QC checklist items complete.
2015-02-25 Fixed qc issues.
2015-03-03 FIxed qc issues
2015-03-23 Fixed USB alignment issue.
2015-04-13 Moved Sch item.
2015-04-23 Changed font to Vector, and re arranged SPK logo
2015-05-04 created new v23 panel
2015-07-09 Updating README
2015-07-09 Adding license, updating README

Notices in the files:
parts and their libraries:
SparkFun-Connectors: Licensing: CC v3.0 Share-Alike You are welcome to use this library for commercial purposes.
SparkFun-Aesthetics: Released under the Creative Commons Attribution Share-Alike 4.0 License
SparkFun-Aesthetics: https://creativecommons.org/licenses/by-sa/4.0
